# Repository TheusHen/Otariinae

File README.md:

# SeaLion (Otariinae)

SeaLion is my smart aquarium project. It started as “automate a few aquarium tasks” and turned into a full embedded system: custom PCB, separate controller boards, 3D structure, telemetry, relay control, local logging, aquaponics expansion, and a visual status matrix.

The project is intentionally split into two boards:

- **WhaleShark**: the main **ESP32** board that handles Wi‑Fi, API, time sync, automation, and system orchestration.
- **Flux**: the auxiliary **RP2040** board that handles local relays, the **MAX7219 8×8 matrix**, MicroSD logging, and hardware-side failsafe behavior.

I did it this way on purpose. I wanted networking and high-level logic on the main board, while the second board stays focused on the things that need to remain deterministic and safe near the hardware.

---

## What this project does

The goal is to keep the aquarium stable with as little manual work as possible.

That includes:

- continuous circulation
- water and environment monitoring
- relay control for pumps and other loads
- a local matrix display for loading, timers, warnings, and system state
- aquaponics expansion support
- local MicroSD logging
- remote control and telemetry through an HTTP API
- internet time sync through the ESP32 instead of an RTC on Flux

The aquaponics expansion in V1 is simple on purpose. It is basically a switchable timed peristaltic pump that pulls water from the aquarium and waters the plants. That logic lives in the automation layer and runs through a dedicated Flux relay output.

---

## Architecture

| Block | Controller | Role |
|---|---|---|
| WhaleShark | ESP32 | Wi‑Fi, API, NTP, automation, sensor aggregation, policy |
| Flux | RP2040 | Relay control, MAX7219 rendering, MicroSD logging, failsafe |
| Matrix | MAX7219 | Boot animations, status icons, scrolling text, timers |
| Aquaponics module | Flux relay output | Timed watering of the plant bed |

### Why this split exists

The ESP32 is the system brain. It is much better for:

- network access
- NTP time synchronization
- exposing an API
- coordinating all modules
- future dashboard integration

Flux is the hardware-side executor. It is better for:

- direct relay outputs
- keeping outputs alive in a safe state if the main board disappears
- driving the matrix without blocking the network stack
- logging locally on MicroSD

That separation also helps wiring. The noisy hardware can stay near the board that is meant to switch it.

---

## MAX7219 matrix

Flux controls an **8×8 matrix through the MAX7219**.

This matrix is not just decorative. It is used to display:

- loading during boot
- Wi‑Fi / ready / alert states
- timer countdowns
- short scrolling messages
- icons for pump, water, warning, and plant state

The firmware maps the matrix logically according to the schematic convention you used:

- rows: `ROW0` to `ROW7`
- columns: `COL7` to `COL0`

That means the firmware intentionally mirrors the logical X axis so the matrix behaves like the schematic view instead of whatever random hardware orientation would otherwise appear on the first try.

---

## Current V1 behavior

### Main aquarium pump

The main circulation pump is treated as a **normally-on output**.

That is the safest default for keeping water moving and helping filtration and oxygen exchange. In automatic mode, the firmware keeps it enabled unless there is a condition that strongly suggests protecting hardware from dry run, such as a low-level alarm.

### Aquaponics pump

The aquaponics expansion is handled by a dedicated Flux relay.

Default V1 policy:

- enabled during daytime window
- runs in short timed pulses
- skipped if the aquarium is in a low-level condition
- controlled by WhaleShark, switched by Flux

Those values are easy to change in the config files once the real flow rate is tested.

---

## Firmware layout

### WhaleShark / ESP32

Main responsibilities:

- connect to Wi‑Fi
- sync time from NTP
- read local sensors
- decide relay states
- expose HTTP API endpoints
- optionally protect endpoints with an API secret
- send commands and time updates to Flux over I2C

Important files:

- `firmware/ESP32/include/pins.h`
- `firmware/ESP32/include/config.h`
- `firmware/ESP32/src/main.cpp`

### Flux / RP2040

Main responsibilities:

- receive commands from WhaleShark over I2C
- drive relays
- drive the MAX7219 matrix
- log to MicroSD
- keep safe defaults if communication is lost

Important files:

- `firmware/RP2040(Flux)/include/pins.h`
- `firmware/RP2040(Flux)/include/config.h`
- `firmware/RP2040(Flux)/src/main.cpp`

Protocol notes:

- `firmware/PROTOCOL.md`

Board-to-board wiring notes:

- `docs/CONNECTIONS_FLUX_TO_WHALE.md`

---

## API

WhaleShark exposes a small V1 HTTP API.

Implemented endpoints:

- `GET /api/v1/ping`
- `GET /api/v1/status`
- `GET /api/v1/sensors`
- `POST /api/v1/mode?value=auto|manual|maintenance`
- `POST /api/v1/relay?name=main_pump|aquaponics|spare1|spare2&state=on|off`
- `POST /api/v1/matrix/text?text=HELLO`
- `POST /api/v1/matrix/timer?seconds=90`

### Optional secret

A V1 dashboard does not exist yet, but the firmware already supports an optional API secret.

Set `API_SECRET` in:

- `firmware/ESP32/include/config.h`

If it is set, requests must include:

- `X-API-Key: <your secret>`

If it is left empty, the API is open on the local network.

---

## Inter-board connection

The recommended connection for V1 is:

- I2C
- one interrupt/status line
- one enable/maintenance line
- shared ground
- 5V power from a single source

Recommended mapping:

| WhaleShark (ESP32) | Flux (RP2040) | Purpose |
|---|---|---|
| GPIO21 | GPIO4 | I2C SDA |
| GPIO22 | GPIO5 | I2C SCL |
| GPIO27 | GPIO14 | Flux interrupt / status |
| GPIO26 | GPIO15 | Flux enable / maintenance |
| 5V | VBUS / 5V in | power |
| GND | GND | common reference |

More detail is in:

- `docs/CONNECTIONS_FLUX_TO_WHALE.md`

---

## Mechanical side

The physical design uses a printed upper and lower structure with an acrylic middle body, mounting points, and space for cables, sensors, pumps, and boards.

### Structure 3D

### Electrical bay

---

## PCB

### Schematic

### Layout

### Board 3D renders

---

## Notes about calibration

The firmware already includes the structure for:

- pH
- TDS
- turbidity
- water level
- water temperature

The analog conversions are present as practical V1 defaults, but they still need final real-world calibration against the exact probes and boards used in the hardware.

That part is normal. The project can boot, talk, switch, and show state without final calibration, but trustworthy chemistry values need calibration with the physical sensors.

---

## V1 priorities

The current focus is not a cloud product. The priority is:

1. boot reliably
2. connect both boards
3. read sensors
4. keep the aquarium alive safely
5. show useful local feedback on the matrix
6. expose a usable local API
7. leave room for a future dashboard

That is the point of this revision: get a strong first real hardware/software foundation instead of pretending the hard parts do not exist.

https://stpeter.im/writings/essays/publicdomain.html

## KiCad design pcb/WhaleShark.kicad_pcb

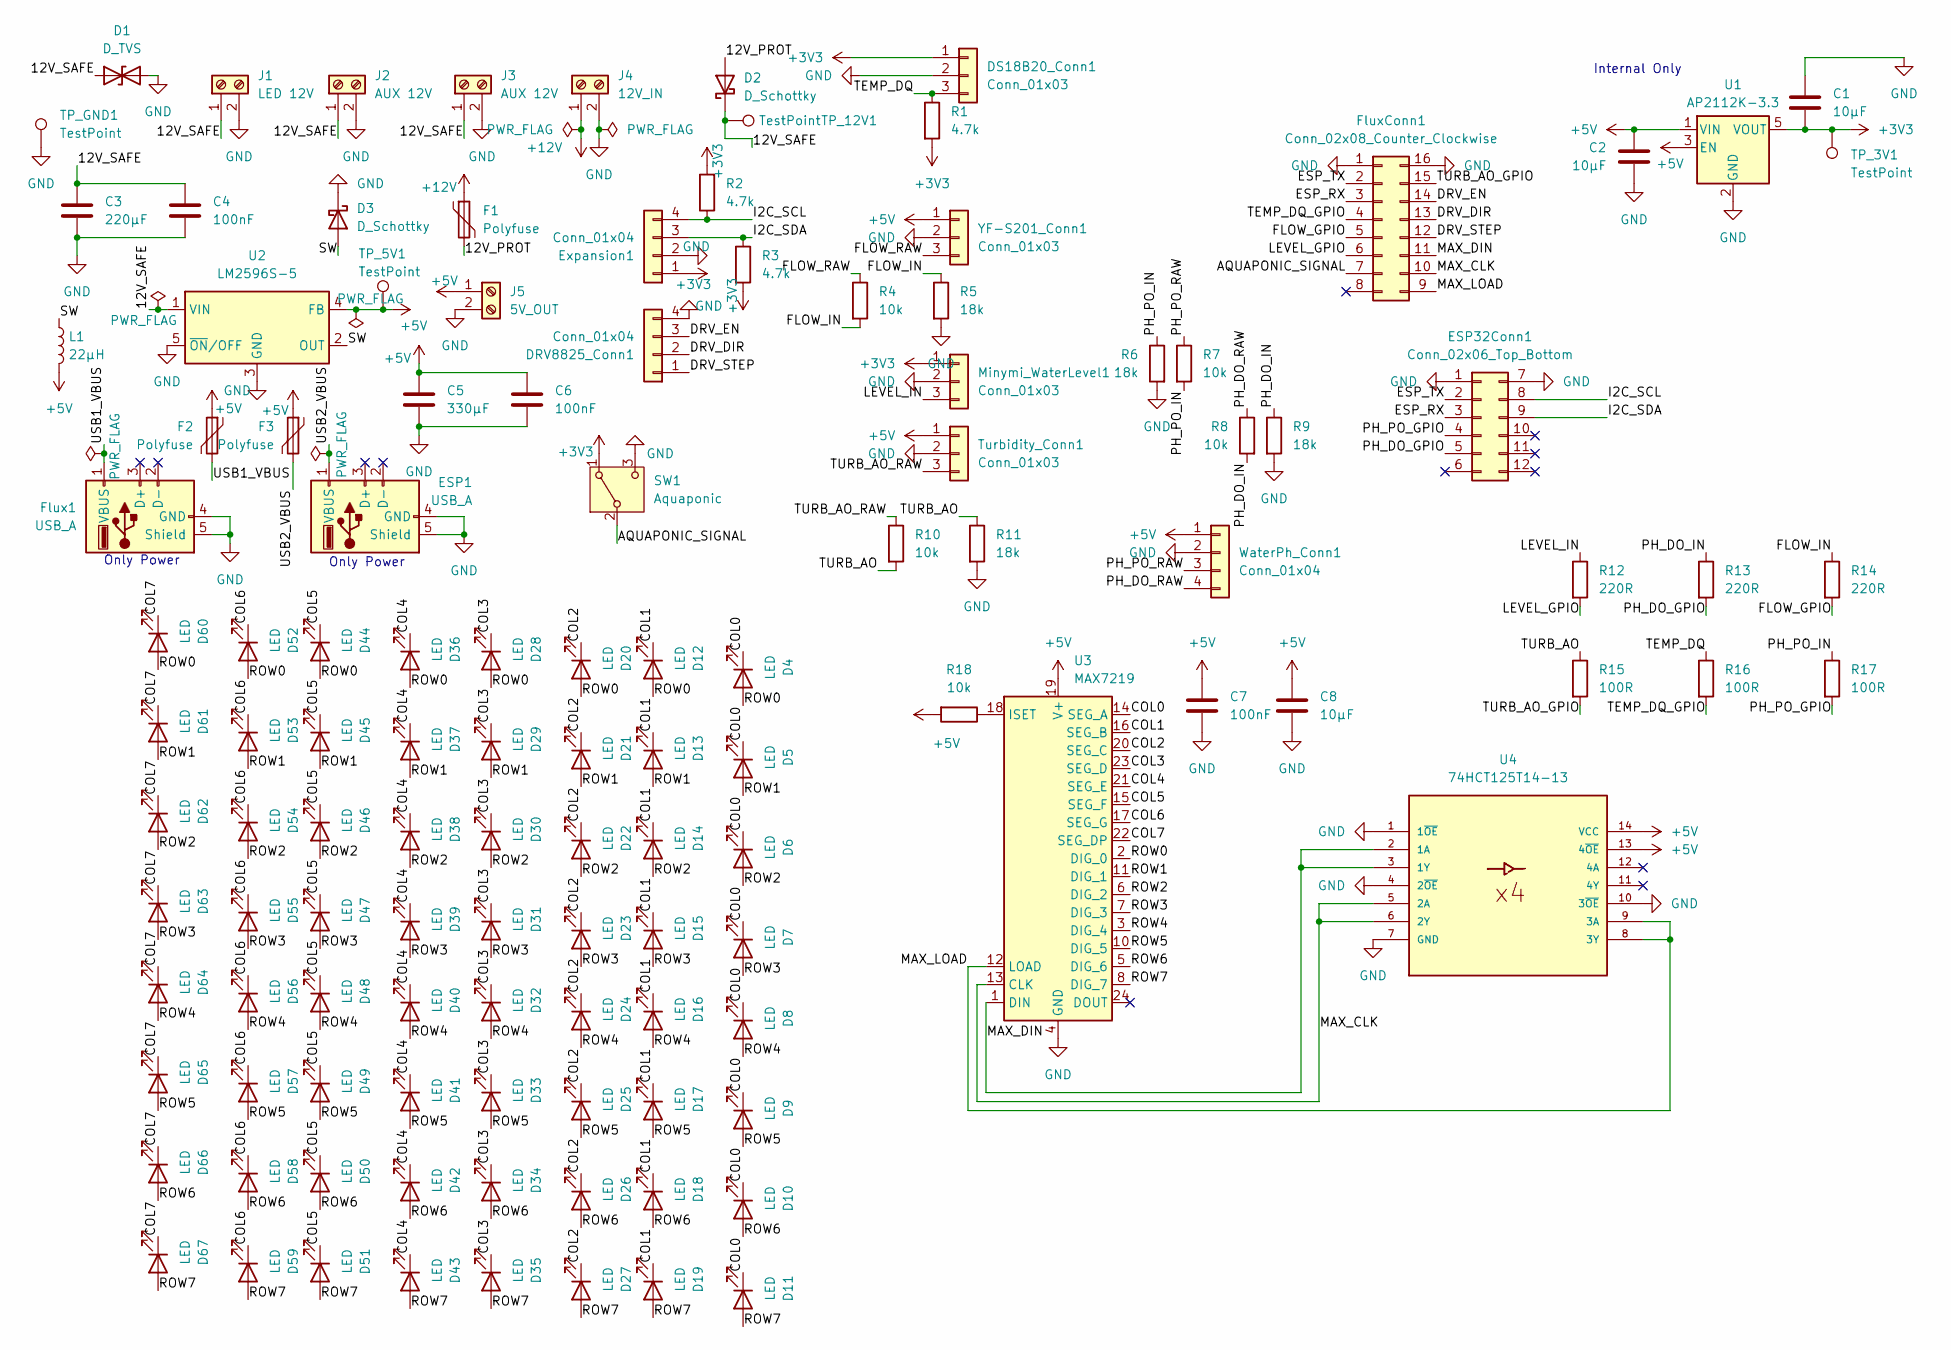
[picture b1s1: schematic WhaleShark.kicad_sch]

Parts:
C1, C2, C8: 10µF; C_1206_3216Metric
C3: 220µF; CP_Radial_D8.0mm_P3.50mm
C4, C6, C7: 100nF; C_0805_2012Metric
C5: 330µF; CP_Radial_D10.0mm_P5.00mm
D1: D_TVS; D_SMA
D2, D3: D_Schottky; D_SMA
D4, D5, D6, D7, D8, D9, D10, D11, D12, D13, D14, D15, D16, D17, D18, D19, D20, D21, D22, D23, D24, D25, D26, D27, D28, D29, D30, D31, D32, D33, D34, D35, D36, D37, D38, D39, D40, D41, D42, D43, D44, D45, D46, D47, D48, D49, D50, D51, D52, D53, D54, D55, D56, D57, D58, D59, D60, D61, D62, D63, D64, D65, D66, D67: LED; LED_0805_2012Metric
DRV8825_Conn1: Conn_01x04; JST_B4B-XH-A
DS18B20_Conn1: Conn_01x03; JST_B3B-XH-A
ESP1: USB_A; USB_A_Molex_105057_Vertical
ESP32Conn1: Conn_02x06_Top_Bottom; PinHeader_2x06_P2.54mm_Vertical
Expansion1: Conn_01x04; JST_B4B-XH-A
F1, F2, F3: Polyfuse; Fuse_1812_4532Metric
Flux1: USB_A; USB_A_Molex_105057_Vertical
FluxConn1: Conn_02x08_Counter_Clockwise; PinHeader_2x08_P2.54mm_Vertical
J1: LED 12V; HANDSON_KF301-2P
J2, J3: AUX 12V; HANDSON_KF301-2P
J4: 12V_IN; HANDSON_KF301-2P
J5: 5V_OUT; HANDSON_KF301-2P
L1: 22µH; L_6.3x6.3_H3
Minymi_WaterLevel1: Conn_01x03; JST_B3B-XH-A
R1, R2, R3: 4.7k; R_0805_2012Metric
R4, R7, R8, R10, R18: 10k; R_0805_2012Metric
R5, R6, R9, R11: 18k; R_0805_2012Metric
R12, R13, R14: 220R; R_0805_2012Metric
R15, R16, R17: 100R; R_0805_2012Metric
SW1: Aquaponic; 450405020524
TP_3V1, TP_5V1, TP_12V1: TestPoint; TestPoint_Pad_D2.0mm
TP_GND1: TestPoint; TestPoint_Pad_D2.0mm
Turbidity_Conn1: Conn_01x03; JST_B3B-XH-A
U1: AP2112K-3.3; SOT-23-5
U2: LM2596S-5; TO-263-5_TabPin3
U3: MAX7219; SOIC-24W_7.5x15.4mm_P1.27mm
U4: 74HCT125T14-13; TSSOP-14_4.4x5mm_P0.65mm
WaterPh_Conn1: Conn_01x04; JST_B4B-XH-A
YF-S201_Conn1: Conn_01x03; JST_B3B-XH-A

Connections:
+3V3: C1.2, DS18B20_Conn1.1, Expansion1.1, Minymi_WaterLevel1.1, R1.2, R2.2, R3.2, SW1.1 (A), TP_3V1.1, U1.5 (VOUT)
+5V: C2.1, C5.1, C6.1, C7.1, C8.1, F2.1, F3.1, J5.1, L1.2, R18.2, TP_5V1.1, Turbidity_Conn1.1, U1.1 (VIN), U1.3 (EN), U2.4 (FB), U3.19 (V+), U4.13 (4~OE), U4.14 (VCC), WaterPh_Conn1.1, YF-S201_Conn1.1
+12V: F1.1, J4.1
/12V_PROT: D2.2 (A), F1.2
/12V_SAFE: C3.1, C4.1, D1.1 (A1), D2.1 (K), J1.1, J2.1, J3.1, TP_12V1.1, U2.1 (VIN)
/AQUAPONIC_SIGNAL: FluxConn1.7, SW1.2 (B)
/COL0: D4.1 (K), D5.1 (K), D6.1 (K), D7.1 (K), D8.1 (K), D9.1 (K), D10.1 (K), D11.1 (K), U3.14 (SEG_A)
/COL1: D12.1 (K), D13.1 (K), D14.1 (K), D15.1 (K), D16.1 (K), D17.1 (K), D18.1 (K), D19.1 (K), U3.16 (SEG_B)
/COL2: D20.1 (K), D21.1 (K), D22.1 (K), D23.1 (K), D24.1 (K), D25.1 (K), D26.1 (K), D27.1 (K), U3.20 (SEG_C)
/COL3: D28.1 (K), D29.1 (K), D30.1 (K), D31.1 (K), D32.1 (K), D33.1 (K), D34.1 (K), D35.1 (K), U3.23 (SEG_D)
/COL4: D36.1 (K), D37.1 (K), D38.1 (K), D39.1 (K), D40.1 (K), D41.1 (K), D42.1 (K), D43.1 (K), U3.21 (SEG_E)
/COL5: D44.1 (K), D45.1 (K), D46.1 (K), D47.1 (K), D48.1 (K), D49.1 (K), D50.1 (K), D51.1 (K), U3.15 (SEG_F)
/COL6: D52.1 (K), D53.1 (K), D54.1 (K), D55.1 (K), D56.1 (K), D57.1 (K), D58.1 (K), D59.1 (K), U3.17 (SEG_G)
/COL7: D60.1 (K), D61.1 (K), D62.1 (K), D63.1 (K), D64.1 (K), D65.1 (K), D66.1 (K), D67.1 (K), U3.22 (SEG_DP)
/DRV_DIR: DRV8825_Conn1.2, FluxConn1.13
/DRV_EN: DRV8825_Conn1.3, FluxConn1.14
/DRV_STEP: DRV8825_Conn1.1, FluxConn1.12
/ESP_RX: ESP32Conn1.3, FluxConn1.3
/ESP_TX: ESP32Conn1.2, FluxConn1.2
/FLOW_GPIO: FluxConn1.5, R14.2
/FLOW_IN: R4.2, R5.1, R14.1
/FLOW_RAW: R4.1, YF-S201_Conn1.3
/I2C_SCL: ESP32Conn1.8, Expansion1.4, R2.1
/I2C_SDA: ESP32Conn1.9, Expansion1.3, R3.1
/LEVEL_GPIO: FluxConn1.6, R12.2
/LEVEL_IN: Minymi_WaterLevel1.3, R12.1
/MAX_CLK: FluxConn1.10, U3.13 (CLK), U4.5 (2A), U4.6 (2Y)
/MAX_DIN: FluxConn1.11, U3.1 (DIN), U4.2 (1A), U4.3 (1Y)
/MAX_LOAD: FluxConn1.9, U3.12 (LOAD), U4.8 (3Y), U4.9 (3A)
/PH_DO_GPIO: ESP32Conn1.5, R13.2
/PH_DO_IN: R8.2, R9.1, R13.1
/PH_DO_RAW: R8.1, WaterPh_Conn1.4
/PH_PO_GPIO: ESP32Conn1.4, R17.2
/PH_PO_IN: R6.1, R7.2, R17.1
/PH_PO_RAW: R7.1, WaterPh_Conn1.3
/ROW0: D4.2 (A), D12.2 (A), D20.2 (A), D28.2 (A), D36.2 (A), D44.2 (A), D52.2 (A), D60.2 (A), U3.2 (DIG_0)
/ROW1: D5.2 (A), D13.2 (A), D21.2 (A), D29.2 (A), D37.2 (A), D45.2 (A), D53.2 (A), D61.2 (A), U3.11 (DIG_1)
/ROW2: D6.2 (A), D14.2 (A), D22.2 (A), D30.2 (A), D38.2 (A), D46.2 (A), D54.2 (A), D62.2 (A), U3.6 (DIG_2)
/ROW3: D7.2 (A), D15.2 (A), D23.2 (A), D31.2 (A), D39.2 (A), D47.2 (A), D55.2 (A), D63.2 (A), U3.7 (DIG_3)
/ROW4: D8.2 (A), D16.2 (A), D24.2 (A), D32.2 (A), D40.2 (A), D48.2 (A), D56.2 (A), D64.2 (A), U3.3 (DIG_4)
/ROW5: D9.2 (A), D17.2 (A), D25.2 (A), D33.2 (A), D41.2 (A), D49.2 (A), D57.2 (A), D65.2 (A), U3.10 (DIG_5)
/ROW6: D10.2 (A), D18.2 (A), D26.2 (A), D34.2 (A), D42.2 (A), D50.2 (A), D58.2 (A), D66.2 (A), U3.5 (DIG_6)
/ROW7: D11.2 (A), D19.2 (A), D27.2 (A), D35.2 (A), D43.2 (A), D51.2 (A), D59.2 (A), D67.2 (A), U3.8 (DIG_7)
/SW: D3.2 (A), L1.1, U2.2 (OUT)
/TEMP_DQ: DS18B20_Conn1.3, R1.1, R16.1
/TEMP_DQ_GPIO: FluxConn1.4, R16.2
/TURB_AO: R10.2, R11.1, R15.1
/TURB_AO_GPIO: FluxConn1.15, R15.2
/TURB_AO_RAW: R10.1, Turbidity_Conn1.3
/USB1_VBUS: F2.2, Flux1.1 (VBUS)
/USB2_VBUS: ESP1.1 (VBUS), F3.2
GND: C1.1, C2.2, C3.2, C4.2, C5.2, C6.2, C7.2, C8.2, D1.2 (A2), D3.1 (K), DRV8825_Conn1.4, DS18B20_Conn1.2, ESP1.4 (GND), ESP1.5 (Shield), ESP32Conn1.1, ESP32Conn1.7, Expansion1.2, Flux1.4 (GND), Flux1.5 (Shield), FluxConn1.1, FluxConn1.16, J1.2, J2.2, J3.2, J4.2, J5.2, Minymi_WaterLevel1.2, R5.2, R6.2, R9.2, R11.2, SW1.3 (C), TP_GND1.1, Turbidity_Conn1.2, U1.2 (GND), U2.3 (GND), U2.5 (~ON/OFF), U3.4 (GND), U3.9 (GND), U4.1 (1~OE), U4.4 (2~OE), U4.7 (GND), U4.10 (3~OE), WaterPh_Conn1.2, YF-S201_Conn1.2
unnamed: R18.1, U3.18 (ISET)

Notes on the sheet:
Internal Only
Only Power

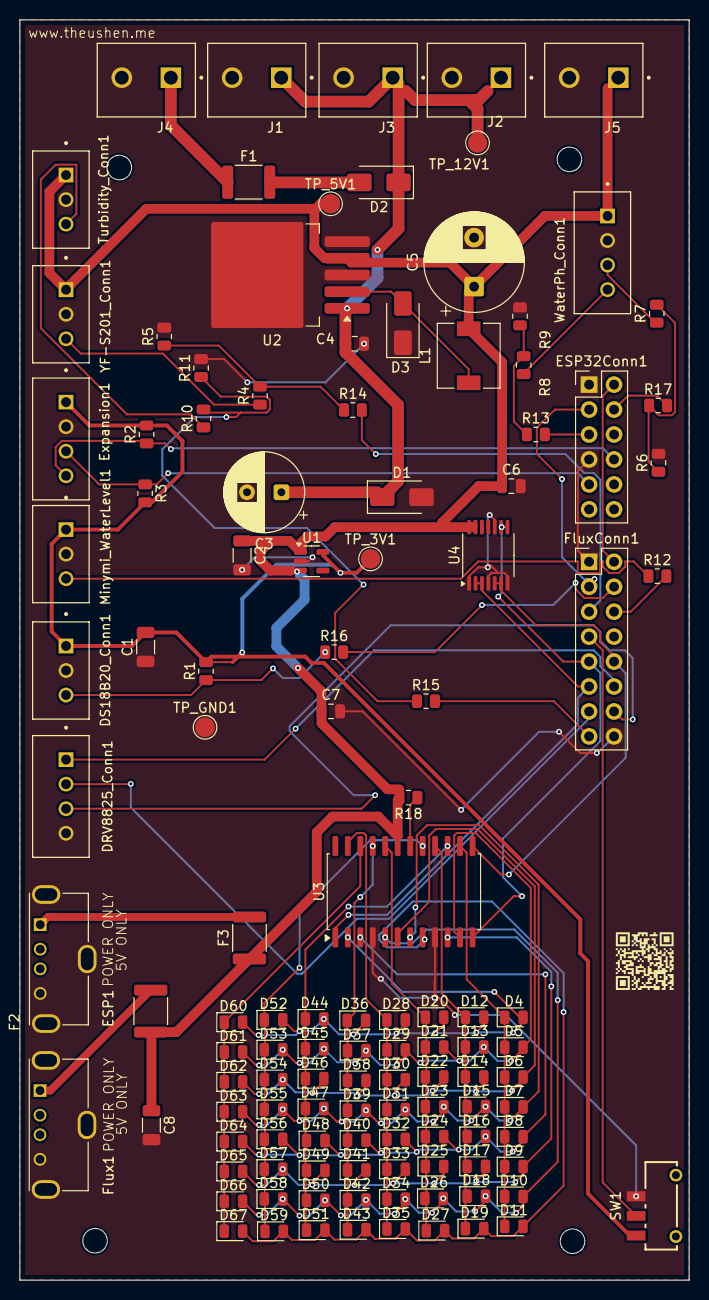
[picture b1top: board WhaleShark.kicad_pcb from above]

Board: 2 copper layers, 68.2 x 128.3 mm, 122 parts (0 on the bottom side), 53 nets.

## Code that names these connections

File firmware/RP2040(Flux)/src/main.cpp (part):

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public:
  void begin() {
    pinMode(Pins::MAX_CS, OUTPUT);
    pinMode(Pins::MAX_CLK, OUTPUT);
    pinMode(Pins::MAX_DIN, OUTPUT);
    SPI.setRX(Pins::SD_MISO);
    SPI.setTX(Pins::MAX_DIN);
    SPI.setSCK(Pins::MAX_CLK);
    SPI.begin(false);
    writeReg(0x0F, 0x00); // display test off
    writeReg(0x0C, 0x01); // shutdown off
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
  // Logical coordinates match the schematic view requested by the project:
  // x grows left->right, y grows top->bottom.
  // The schematic labels are COL7..COL0 from left to right,
  // so physical bit order is mirrored here intentionally.
  void setPixel(uint8_t x, uint8_t y, bool on) {
    if (x > 7 || y > 7) return;
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    logLine("epoch,millis,relay_mask,matrix_mode,faults,sd_present");
  }

  Wire.setSDA(Pins::I2C_SDA);
  Wire.setSCL(Pins::I2C_SCL);
  Wire.begin(Config::I2C_ADDRESS);
  Wire.onReceive(onReceive);
  Wire.onRequest(onRequest);
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
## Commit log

2026-03-08 Revise BOM.csv with updated product information
    Updated BOM.csv to include new product details and pricing.
2026-03-08 Fix formatting issue in bom_parts_eletrical.csv
2026-03-08 Add BOM files and connection documentation for Flux and WhaleShark integration
2026-03-08 Enhance README.md with structured 3D and PCB images for better visualization
2026-03-09 Add firmware for WhaleShark (ESP32) and RP2040 (Flux) with initial configurations and sensor handling
    - Created pins.h and config.h for both ESP32 and RP2040 with appropriate pin mappings and configuration settings.
    - Implemented main.cpp for ESP32 with WiFi, web server, and sensor management including temperature, pH, TDS, turbidity, and ambient light.
    - Added command protocol for communication with Flux and implemented relay control and automation logic.
    - Developed Max7219Matrix class for handling LED matrix display on RP2040, including drawing icons and scrolling text.
    - Integrated SD card logging functionality in RP2040 firmware.
    - Established I2C communication for both platforms to fac
2026-03-09 Fixed build errors, added new libs and updated .gitignore
2026-03-09 Updated Jornal from Blueprint
